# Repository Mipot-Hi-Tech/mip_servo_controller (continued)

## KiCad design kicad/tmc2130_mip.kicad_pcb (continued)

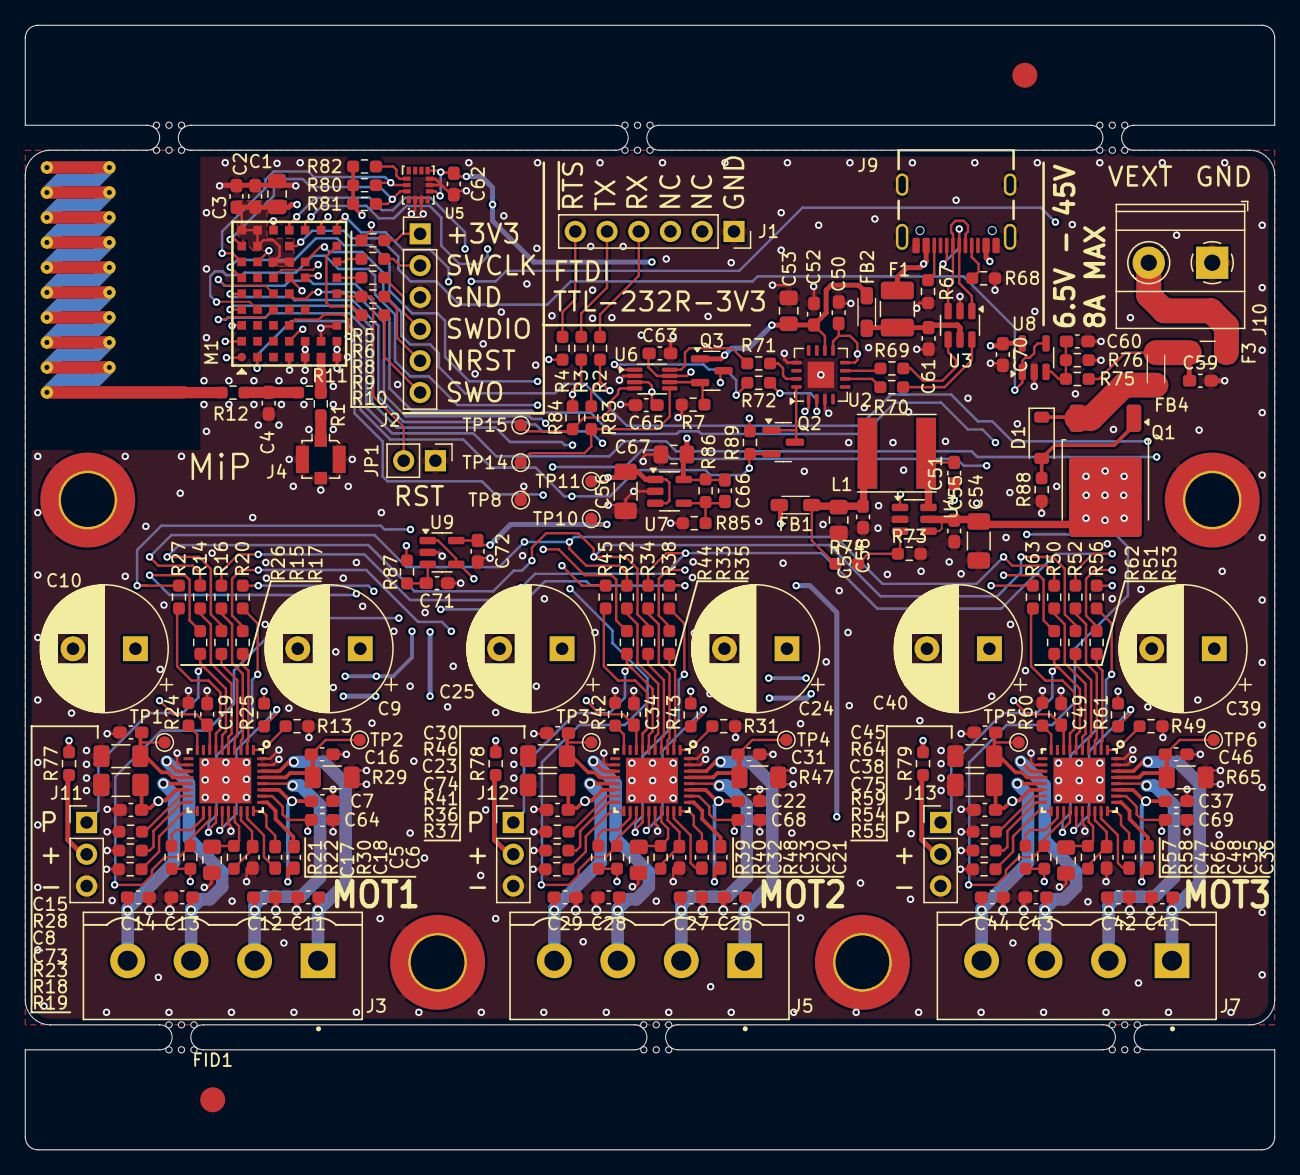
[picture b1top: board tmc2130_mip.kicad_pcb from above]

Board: 4 copper layers, 100.0 x 90.0 mm, 219 parts (0 on the bottom side), 156 nets.

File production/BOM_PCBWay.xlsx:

|  |  | LoRa based triple stepper board PCS BOM
Item # | *Designator | *Qty | Manufacturer | *Mfg Part # | Description / Value | *Package/Footprint | Type | ORDER CODE(MOUSER)
1 | C1,C17,C32,C47,C53,C57,C67 | 7 | MURATA | GRM21BR71C475KE51L | Multilayer Ceramic Capacitors MLCC - SMD/SMT 4.7 uF 16 VDC 10% 0805 X7R | C0805 | SMD | 81-GRM21BR71C475KE1L
2 | C2,C3,C6,C7,C19,C21,C22,C34,C36,C37,C49,C50,C51,C52,C55,C58,C59,C60,C61,C63,C64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 | 30 | SAMSUNG | CL10B104KC8NNNC | Multilayer Ceramic Capacitors MLCC - SMD/SMT 100nF+/-10% 100V X7R 0603 | C0603 | SMD | 187-CL10B104KC8NNNC
3 | C5,C20,C35 | 3 | TDK | C1608X7R1H223K080AA | Multilayer Ceramic Capacitors MLCC - SMD/SMT 0603 50VDC 22nF 10% X7R 0.8mm | C0603 | SMD | 810-C1608X7R1H223K
4 | C8,C23,C38,C54 | 4 | MURATA | GRM31CZ72A475KE11L | Multilayer Ceramic Capacitors MLCC - SMD/SMT 4.7 uF 100 VDC 10% 1206 X7R | C1206 | SMD | 81-GRM31CZ72A475K11L
5 | C9,C24,C39 | 3 | YAGEO | C0603C221J5GACAUTO7411 | Multilayer Ceramic Capacitors MLCC - SMD/SMT 50V 220pF C0G 0603 5% AEC-Q200 | C0603 | SMD | 667-EEU-FR1J151
6 | C18,C33,CC48 | 3 | SAMSUNG | CL10B474KA8NNNC | Multilayer Ceramic Capacitors MLCC - SMD/SMT 470nF+/-10% 25V X7R 0603 | C0603 | SMD | 187-CL10B474KA8NNNC
7 | C56 | 1 | KEMET | C0603C221J5GACAUTO7411 | Multilayer Ceramic Capacitors MLCC - SMD/SMT 50V 220pF C0G 0603 5% AEC-Q200 | C0603 | SMD | 80-C0603C221J5GAUTLR
8 | D1 | 1 | NEXPERIA | BZT52-C13J | Zener Diodes BZT52-C13/SOD123/SOD2 | SOD-123-2 | SMD | 771-BZT52-C13J
9 | F1 | 1 | LITTLEFUSE | MICROSMD050F-2 | Resettable Fuses - PPTC .5A 13.2V 40A Imax | 1210 | SMD | 650-MICROSMD050F-2
10 | F3 | 1 | BOURNS | SF-1206HH1200R-2 | Surface Mount Fuses 1206 high-current met-foil. 12A | 1206 | SMD | SF-1206HH1200R-2
11 | FB1,FB2,FB4 | 3 | WURTH ELEKTRONIK | 742792030 | Ferrite Beads WE-CBF 3mOhms 10K mA805 AEC-Q200 | 0805 | SMD | 710-742792030
12 | J3,J5,J7 | 3 | PHOENIX CONTACT | 1755752 | Pluggable Terminal Blocks 4 Pos 5.08mm pitch Through Hole Header | Pitch 5.08mm | THT | 651-1755752
13 | J4 | 1 | MOLEX | 73412-0110 | RF Connectors / Coaxial Connectors MCX V PCB JACK SMT 1.25MM MNT HGT |  | SMD | 538-73412-0110
14 | J9 | 1 | GCT | USB4105-GF-A | USB Connectors USB Type C,2.0, Rec,SMT, 0.95mmTH Shell Stakes,G/F,RA,Top Mnt,T&R |  | SMD | 640-USB4105-GF-A
15 | J10 | 1 | PHOENIX CONTACT | 1987096 | Fixed Terminal Blocks MKDSN 2,5/ 2-5,08 SZS-SCREW | Pitch 5.08mm | SMD | 651-1987096
16 | J15,J16,J17 | 3 | PHOENIX CONTACT | 1792265 | Pluggable Terminal Blocks 4 Pos 5.08mm pitch Plug 24-12 AWG Screw |  |  | 651-1792265
17 | L1 | 1 | TAIYO YUDEN | NRS6028T470MMGJ | Power Inductors - SMD 963-LSXND6060WHL470M RPLCMT PN 6028 47uH 390mOhms |  | SMD | 963-NRS6028T470MMGJ
18 | M1 | 1 | MIPOT | 32001505/6CEU | 32001506BEU - MIPOT DUAL CORE LoRa MODULE | LGA | SMD | https://mipot.com/en/products/mip-series/dual-core/32001506deu/
19 | MOT1,MOT2,MOT3 | 3 | ANALOG DEVICES | TMC2130-LA | Motor/Motion/Ignition Controllers & Drivers Silent stepper motor driver 5 to 46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 |  | SMD | 700-TMC2130LA
20 | Q1 | 1 | DIODES INCORPORATED | DMPH6050SK3-13 | MOSFETs MOSFET BVDSS | DPAK-3 | SMD | 621-DMPH6050SK3-13
21 | Q2,Q3 | 2 | DIODES INCORPORATED | BS870-7-F | MOSFETs 60V 310mW | SOT-23-3 | SMD | 621-BS870-F
22 | R2,R3,R4,R5,R6,R8,R9,R10,R14,R15,R16,R17,R20,R26,R27,R32,R33,R34,R35,R38,R44,R4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 | 35 | YAGEO | AC0603JR-0722RL | Thick Film Resistors - SMD 22 Ohms 100 mW 0603 5% AEC-Q200 Standard Power Versi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 | R0603 | SMD | 603-AC0603JR-0722RL
23 | R7,R74,R88 | 3 | YAGEO | RT0603FRE07360KL | Thick Film Resistors - SMD 360k Ohms 100 mW 0603 5% AEC-Q200 Standard Power Ver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 | R0603 | SMD | 603-RT0603FRE07360KL
24 | R11,R12,R13,R18,R19,R23,R25,R31,R36,R37,R41,R43,R49,R54,R55,R59,R61 | 17 | YAGEO | RC0603FR-100RL | Thick Film Resistors - SMD 0 Ohms 100-200mW 0603 1% | R0603 | SMD | 603-RC0603FR-100RL
25 | R21,R22,R39,R40,R57,R58,R87,R89 | 8 | YAGEO | RC0603JR-0710KL | Thick Film Resistors - SMD 10 kOhms 100 mW 0603 5% | R0603 | SMD | 603-RC0603JR-0710KL
26 | R28,R29,R46,R47,R64,R65 | 6 | YAGEO | RL1206FR-070R22L | Current Sense Resistors - SMD 220 mOhms 250mW 1 % 600 ppm/C | R1206 | SMD | 603-RL1206FR070R22L
27 | R30,R48,R66 | 3 | YAGEO | RC0603JR-072R2L | Thick Film Resistors - SMD 2.2 Ohms 100 mW 0603 5% | R0603 | SMD | 603-RC0603JR-072R2L
28 | R67,R68 | 2 | YAGEO | RC0603FR-105K1L | Thick Film Resistors - SMD 5.1kOhms 1/10W 0603 1% | R0603 | SMD | 603-RC0603FR-105K1L
29 | R73,R76 | 2 | YAGEO | RC0402FR-0756K2L | Thick Film Resistors - SMD 56.2 kOhms 62.5mW 0402 1% | R0402 | SMD | 603-RC0402FR-0756K2L
30 | R75 | 1 | YAGEO | RC0603FR-071ML | Thick Film Resistors - SMD 1 MOhms 100mW 0603 1% | R0603 | SMD | 603-RC0603FR-071ML
31 | R85 | 1 | YAGEO | RC0402FR-0718KL | Thick Film Resistors - SMD 18 kOhms 62.5mW 0402 1% | R0402 | SMD | 603-RC0402FR-0718KL
32 | R86 | 1 | YAGEO | RC0402FR-0756K2L | Thick Film Resistors - SMD 56.2 kOhms 62.5mW 0402 1% | R0603 | SMD | 603-RC0402FR-0756K2L
33 | U2 | 1 | FTDI | FT230XQ-R | USB Interface IC USB to Basic Serial UART IC QFN-16 | QFN16 | SMD | 895-FT230XQ-R
34 | U3 | 1 | STMICROELECTRONICS | USBLC6-2SC6 | ESD Protection Diodes / TVS Diodes ESD Protection Low Cap | SOT23-6 | SMD | 511-USBLC6-2SC6
35 | U4 | 1 | TEXAS INSTRUMENTS | LMR51610XDBVR | Switching Voltage Regulators SIMPLE SWITCHER power converter with 4.5V-to-65V 1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 | SOT23-6 | SMD | 595-LMR51610XDBVR
36 | U6 | 1 | TEXAS INSTRUMENTS | TXS0102DCUR | Translation - Voltage Levels 2-Bit Bi-Directional Voltage-Level-Trans | VSSOP-8 | SMD | 595-TXS0102DCUR
37 | U7 | 1 | DIODES INCORPORATED | AP2127K-ADJTRG1 | LDO Voltage Regulators 300mA CMOS LDO 2.5V to 6V | SOT23-5 | SMD | 621-AP2127K-ADJTRG1
38 | U8,U9 | 2 | MICROCHIP | MCP6001T-E/OT | Operational Amplifiers - Op Amps Single 1.8V 1MHz | SOT23-5 | SMD | 579-MCP6001T-E/OT

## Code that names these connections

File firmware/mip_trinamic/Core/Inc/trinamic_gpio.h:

/**
* Copyright (c) Mipot S.p.A. All rights reserved.
*
* BSD-3-Clause
*
* Redistribution and use in source and binary forms, with or without
* modification, are permitted provided that the following conditions are met:
*
* 1. Redistributions of source code must retain the above copyright
*    notice, this list of conditions and the following disclaimer.
*
* 2. Redistributions in binary form must reproduce the above copyright
*    notice, this list of conditions and the following disclaimer in the
*    documentation and/or other materials provided with the distribution.
*
* 3. Neither the name of the copyright holder nor the names of its
*    contributors may be used to endorse or promote products derived from
*    this software without specific prior written permission.
*
* THIS SOFTWARE IS PROVIDED BY THE COPYRIGHT HOLDERS AND CONTRIBUTORS
* "AS IS" AND ANY EXPRESS OR IMPLIED WARRANTIES, INCLUDING, BUT NOT
* LIMITED TO, THE IMPLIED WARRANTIES OF MERCHANTABILITY AND FITNESS
* FOR A PARTICULAR PURPOSE ARE DISCLAIMED. IN NO EVENT SHALL THE
* COPYRIGHT HOLDER OR CONTRIBUTORS BE LIABLE FOR ANY DIRECT, INDIRECT,
* INCIDENTAL, SPECIAL, EXEMPLARY, OR CONSEQUENTIAL DAMAGES
* (INCLUDING, BUT NOT LIMITED TO, PROCUREMENT OF SUBSTITUTE GOODS OR
* SERVICES; LOSS OF USE, DATA, OR PROFITS; OR BUSINESS INTERRUPTION)
* HOWEVER CAUSED AND ON ANY THEORY OF LIABILITY, WHETHER IN CONTRACT,
* STRICT LIABILITY, OR TORT (INCLUDING NEGLIGENCE OR OTHERWISE) ARISING
* IN ANY WAY OUT OF THE USE OF THIS SOFTWARE, EVEN IF ADVISED OF THE
* POSSIBILITY OF SUCH DAMAGE.
*
* @file       mip_b.c
* @date
* @version
*
*/

#ifndef CORE_INC_TRINAMIC_GPIO_H_
#define CORE_INC_TRINAMIC_GPIO_H_

/*******************************************************************************
 * Included files
 *****************************************************************************/
#include "main.h"

/*******************************************************************************
 * Definitions
 ******************************************************************************/

#define TRINAMIC_MOT0_ID 0
#define TRINAMIC_MOT1_ID 1
#define TRINAMIC_MOT2_ID 2

/* MOT 0 */
#define DRV0_STEP_Pin			GPIO_PIN_10
#define DRV0_STEP_Port 			GPIOB

#define DRV0_DIR_Pin			GPIO_PIN_6
#define DRV0_DIR_Port  			GPIOA

#define DRV0_EN_Pin				GPIO_PIN_5
#define DRV0_EN_Port  			GPIOA

#define DRV0_DIAGNOSTIC_Pin		GPIO_PIN_2
#define DRV0_DIAGNOSTIC_Port  	GPIOB

#define DRV0_SPI_NSS_Pin		GPIO_PIN_4
#define DRV0_SPI_NSS_Port  		GPIOA

/* MOT 1 */
#define DRV1_STEP_Pin			GPIO_PIN_11
#define DRV1_STEP_Port 			GPIOB

#define DRV1_DIR_Pin			GPIO_PIN_14
#define DRV1_DIR_Port  			GPIOB

#define DRV1_EN_Pin		        GPIO_PIN_4
#define DRV1_EN_Port	        GPIOB

#define DRV1_DIAGNOSTIC_Pin		GPIO_PIN_3
#define DRV1_DIAGNOSTIC_Port	GPIOA

#define DRV1_SPI_NSS_Pin		GPIO_PIN_12
#define DRV1_SPI_NSS_Port  		GPIOB

/* MOT 2 */
#define DRV2_EN_Pin		        GPIO_PIN_1
#define DRV2_EN_Port	        GPIOA

#define DRV2_STEP_Pin		    GPIO_PIN_0
#define DRV2_STEP_Port	        GPIOA

#define DRV2_DIR_Pin			GPIO_PIN_5
#define DRV2_DIR_Port 			GPIOB

#define DRV2_DIAGNOSTIC_Pin		GPIO_PIN_15
#define DRV2_DIAGNOSTIC_Port	GPIOA

#define DRV2_SPI_NSS_Pin		GPIO_PIN_12
#define DRV2_SPI_NSS_Port  		GPIOA

/* SPI */
#define SPI2_MOSI_Pin			GPIO_PIN_3
#define SPI2_MOSI_Port  		GPIOC

#define SPI2_MISO_Pin			GPIO_PIN_2
#define SPI2_MISO_Port  		GPIOC

#define SPI2_CLK_Pin			GPIO_PIN_9
#define SPI2_CLK_Port  		    GPIOA

/* FTDI */
#define MOD_TX_Pin				GPIO_PIN_0
#define MOD_TX_Port				GPIOC

#define MOD_RX_Pin				GPIO_PIN_1
#define MOD_RX_Port				GPIOC

#define MOD_NWAKE_Pin			GPIO_PIN_7
#define MOD_NWAKE_Port			GPIOA

/* IIC */
#define IIC_SCL_Pin				GPIO_PIN_8
#define IIC_SCL_Port			GPIOB

#define IIC_SDA_Pin				GPIO_PIN_9
#define IIC_SDA_Port			GPIOB

/* GPIO DEBUG */
#define GPIO0_NWAKE_Pin			GPIO_PIN_7
#define GPIO0_NWAKE_Port		GPIOA

/* BATTERY MEASUREMENT & DAC */
#define AIN_IREF_MIP_Pin		GPIO_PIN_10
#define AIN_IREF_MIP_Port  		GPIOA

#define VEXT_SENSE_Pin			GPIO_PIN_13
#define VEXT_SENSE_Port  		GPIOB

/*******************************************************************************
* API
******************************************************************************/
void TrinamicGPIO_Init(void);
void TrinamicNSS_Select(uint8_t driver);
void TrinamicNSS_Idle(void);
void TrinamicMotXEnable(uint8_t driver);
void TrinamicMotXDisable(uint8_t driver);

#endif

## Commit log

2025-03-11 deleted diagnosis task
2025-03-13 mot1 now ok, modified systick handler
2025-03-13 modified direction control for stepper
2025-03-13 added shell gif
2025-03-13 shell auto
2025-03-13 readme restored
2025-03-14 add readall register command
2025-04-22 Update LICENSE.md
    LICENSE.md updated.
2025-05-05 ipcc stuck in eeprom write cmd. now ok
2025-07-03 added cli history with character 'ì'
2025-09-25 TIM2 now handles also servos
